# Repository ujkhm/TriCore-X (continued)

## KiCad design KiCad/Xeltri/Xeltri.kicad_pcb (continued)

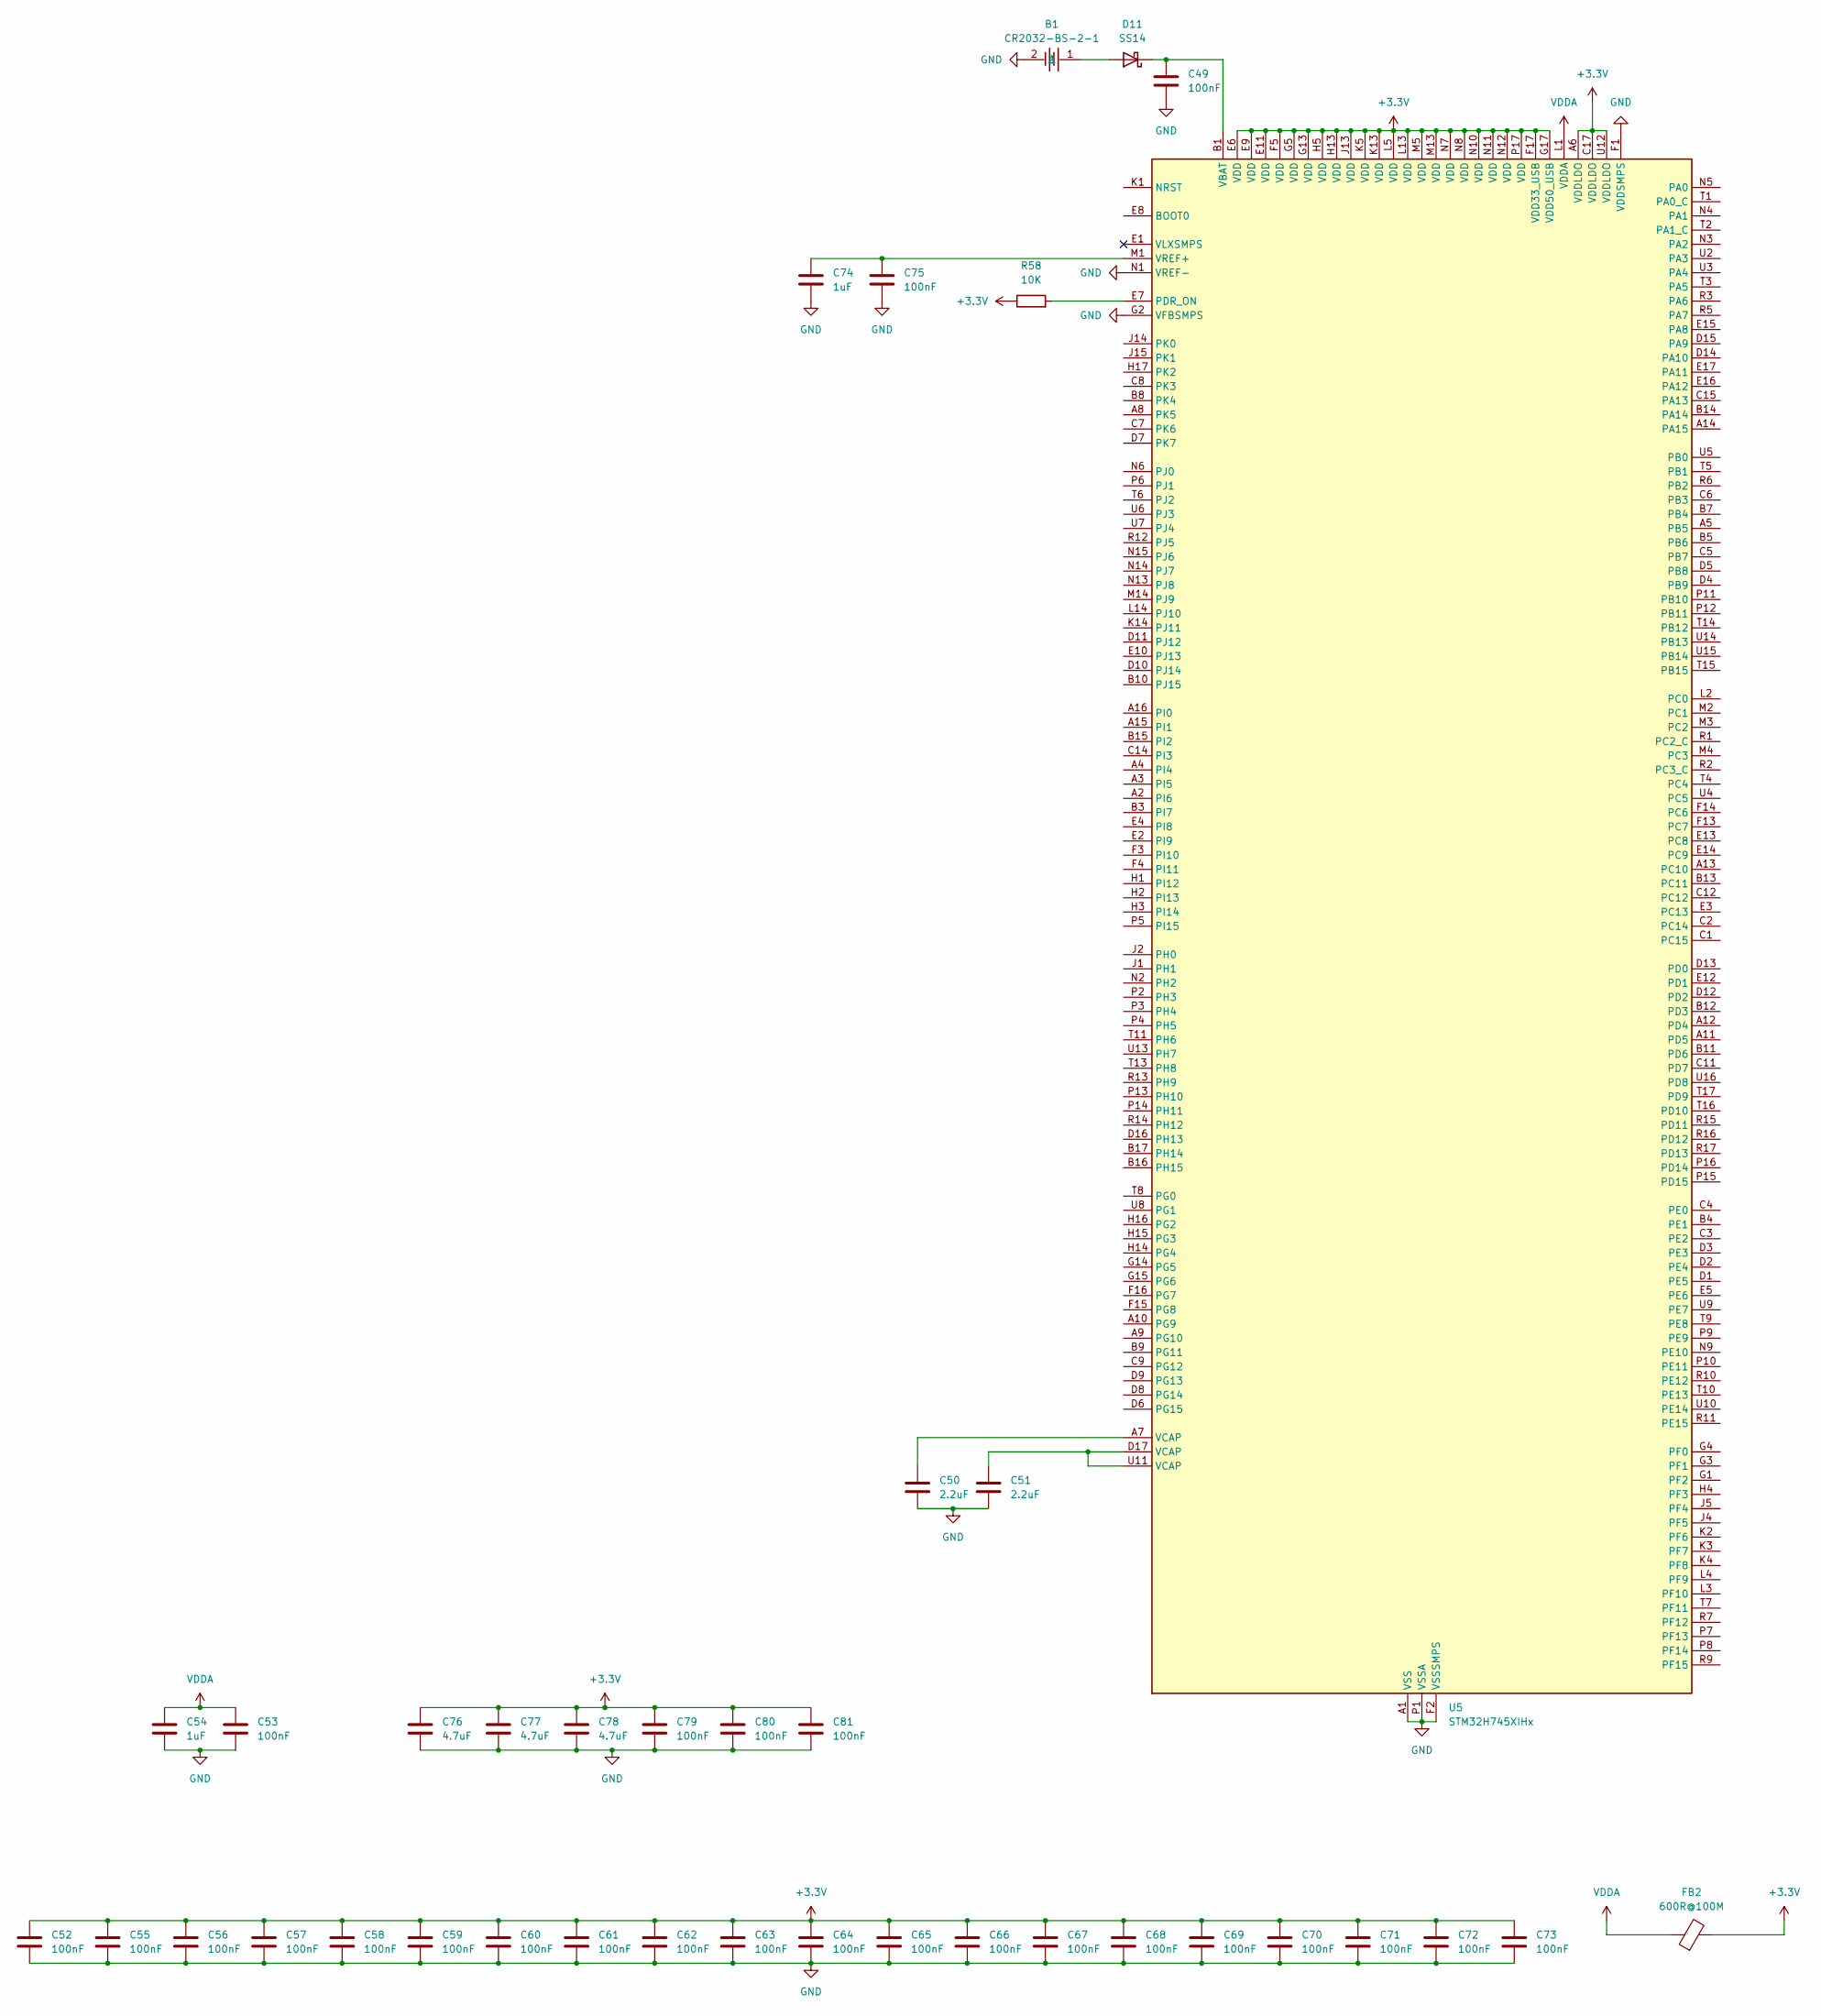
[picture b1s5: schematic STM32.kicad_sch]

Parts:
B1: CR2032-BS-2-1; BAT-TH_BS-2-1; LCSC Part C70376
C49, C52, C53, C55, C56, C57, C58, C59, C60, C61, C62, C63, C64, C65, C66, C67, C68, C69, C70, C71, C72, C73, C75, C79, C80, C81: 100nF; C_0402_1005Metric
C50, C51: 2.2uF; C_0402_1005Metric
C54, C74: 1uF; C_0402_1005Metric
C76, C77, C78: 4.7uF; C_0805_2012Metric
D11: SS14; D_SMA
FB2: 600R@100M; L_0402_1005Metric
R58: 10K; R_0402_1005Metric
U5: STM32H745XIHx; TFBGA-265_14x14mm_Layout17x17_P0.8mm

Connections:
+3.3V: C52.1, C55.1, C56.1, C57.1, C58.1, C59.1, C60.1, C61.1, C62.1, C63.1, C64.1, C65.1, C66.1, C67.1, C68.1, C69.1, C70.1, C71.1, C72.1, C73.1, C76.1, C77.1, C78.1, C79.1, C80.1, C81.1, FB2.2, R58.1, U5.A6 (VDDLDO), U5.C17 (VDDLDO), U5.E6 (VDD), U5.E9 (VDD), U5.E11 (VDD), U5.F5 (VDD), U5.F17 (VDD33_USB), U5.G5 (VDD), U5.G13 (VDD), U5.G17 (VDD50_USB), U5.H5 (VDD), U5.H13 (VDD), U5.J13 (VDD), U5.K5 (VDD), U5.K13 (VDD), U5.L5 (VDD), U5.L13 (VDD), U5.M5 (VDD), U5.M13 (VDD), U5.N7 (VDD), U5.N8 (VDD), U5.N10 (VDD), U5.N11 (VDD), U5.N12 (VDD), U5.P17 (VDD), U5.U12 (VDDLDO); also elsewhere on the board
GND: B1.2, C49.2, C50.1, C51.2, C52.2, C53.2, C54.2, C55.2, C56.2, C57.2, C58.2, C59.2, C60.2, C61.2, C62.2, C63.2, C64.2, C65.2, C66.2, C67.2, C68.2, C69.2, C70.2, C71.2, C72.2, C73.2, C74.2, C75.2, C76.2, C77.2, C78.2, C79.2, C80.2, C81.2, U5.A1 (VSS), U5.A17 (VSS), U5.B2 (VSS), U5.B6 (VSS), U5.C10 (VSS), U5.C13 (VSS), U5.C16 (VSS), U5.F1 (VDDSMPS), U5.F2 (VSSSMPS), U5.G2 (VFBSMPS), U5.G7 (VSS), U5.G8 (VSS), U5.G9 (VSS), U5.G10 (VSS), U5.G11 (VSS), U5.G16 (VSS), U5.H7 (VSS), U5.H8 (VSS), U5.H9 (VSS), U5.H10 (VSS), U5.H11 (VSS), U5.J3 (VSS), U5.J7 (VSS), U5.J8 (VSS), U5.J9 (VSS), U5.J10 (VSS), U5.J11 (VSS), U5.J16 (VSS), U5.J17 (VSS), U5.K7 (VSS), U5.K8 (VSS), U5.K9 (VSS), U5.K10 (VSS), U5.K11 (VSS), U5.K15 (VSS), U5.L7 (VSS), U5.L8 (VSS), U5.L9 (VSS), U5.L10 (VSS), U5.L11 (VSS), U5.L15 (VSS), U5.M15 (VSS), U5.N1 (VREF-), U5.N16 (VSS), U5.P1 (VSSA), U5.R4 (VSS), U5.R8 (VSS), U5.T12 (VSS), U5.U1 (VSS), U5.U17 (VSS); also elsewhere on the board
unnamed: C50.2, U5.A7 (VCAP)
unnamed: C51.1, U5.D17 (VCAP), U5.U11 (VCAP)
unnamed: B1.1, D11.2 (A)
unnamed: C49.1, D11.1 (K), U5.B1 (VBAT)
unnamed: R58.2, U5.E7 (PDR_ON)
unnamed: C74.1, C75.1, U5.M1 (VREF+)
VDDA: C53.1, C54.1, FB2.1, U5.L1 (VDDA)

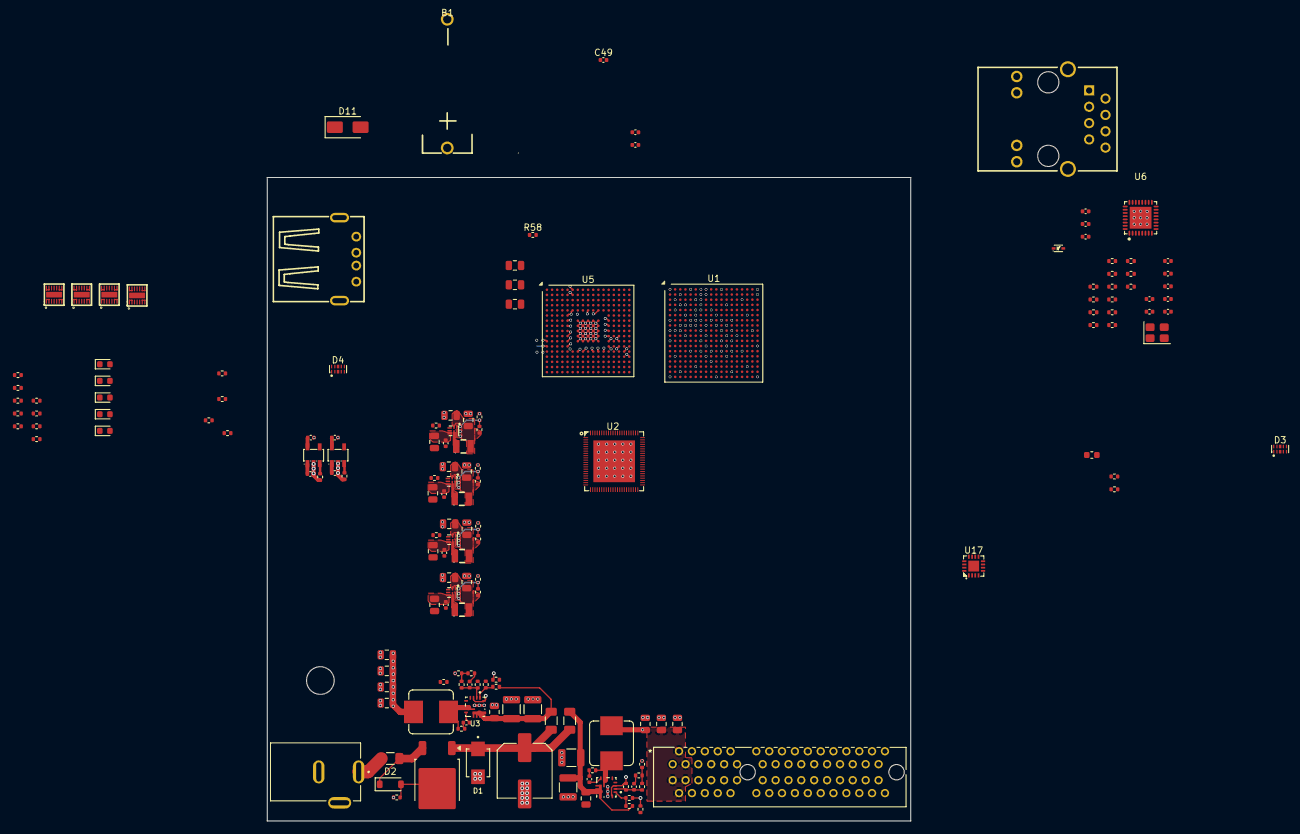
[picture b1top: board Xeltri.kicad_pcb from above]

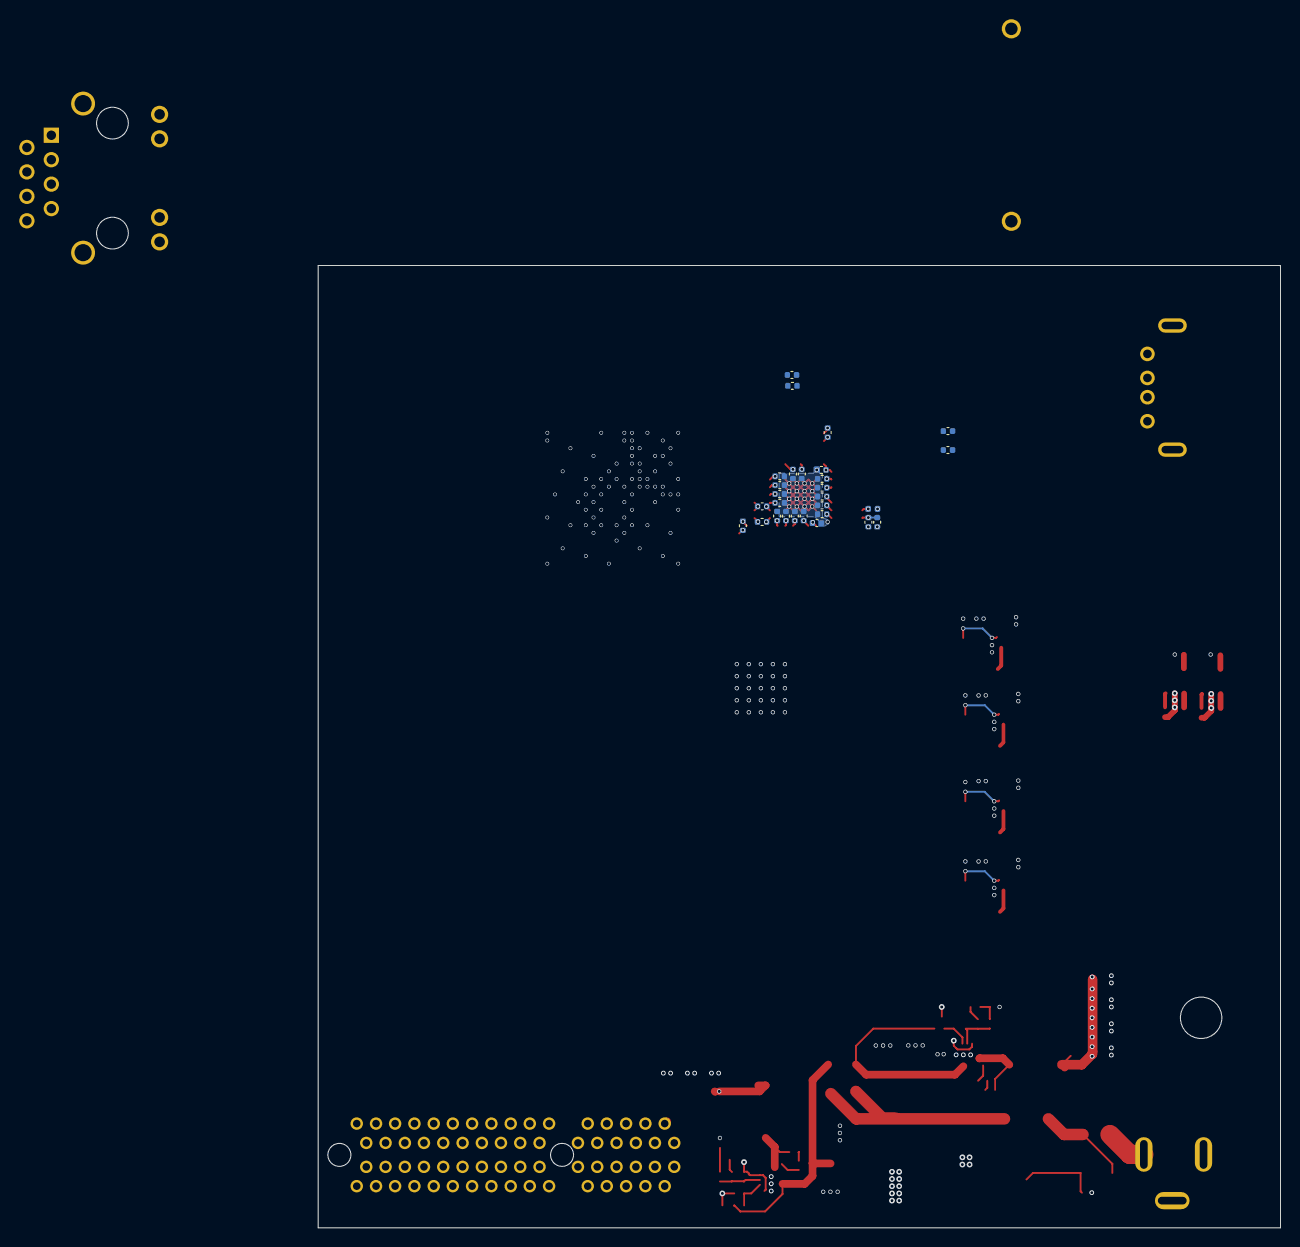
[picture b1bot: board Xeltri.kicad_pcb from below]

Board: 6 copper layers, 100.0 x 100.0 mm, 187 parts (28 on the bottom side), 107 nets.

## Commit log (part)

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2026-06-25 chore: add and structure project-specific .gitignore files
    Move the root level .gitignore to the KiCad subdirectory and introduce specialized .gitignore files for the other subprojects.
    - Move root `.gitignore` to `KiCad/.gitignore`
    - Add `.gitignore` for `FPGA` to filter out Vivado log, journal, and run files
    - Add `.gitignore` for `VSCode/ESP32` to ignore ESP-IDF and PlatformIO build outputs
    - Add `.gitignore` for `VSCode/STM32` to ignore CMake, VS Code IPCH, and compiler outputs (ELF, BIN, HEX)
    This prevents platform-specific build artifacts and IDE cache files from cluttering the repository.
2026-06-25 Update README.md with project details
2026-06-26 docs: improve README layout and update project note
    - Reformat the main description using blockquotes for better readability
    - Move the personal disclaimer into a dedicated "Project Note" section
    - Add a specific project start date (June 25, 2026) to provide context
2026-06-29 feat : create KiCad project and add 5 subsheets (power, RK3568B2, DDR4, FPGA and Debug Interface)
2026-06-29 docs : modify README.md
